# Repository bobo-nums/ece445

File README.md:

# Solar-Powered Traffic Light

Team Members:
- Colin Tarkowski (colinet2)
- Bowen Xiao (bowenx2)
- Richard Przybek (przybek2)

# Problem

Traffic lights are integral to our society, despite their relative lack of innovation over the years. The most significant change has been the switch from incandescent bulbs to LEDs in an attempt to reduce the power consumption of this necessary device. However, this has also led to an increase of light pollution due to the cooler, more intense light emitted by LEDs. They can cause extreme glare and pose a danger to drivers at night. Additionally, the issue of bicyclists and vehicles sharing the road can create many awkward or dangerous situations due to the lack of separation.

# Solution

We propose a solar-powered traffic light system that will solve the issues of drivers and bicyclists sharing the intersection and of light pollution, in addition to reducing consumption of traditional power in two ways. A pressure sensor located near the intersection, such as located upon a nearby curb, will detect whether there is a bicyclist present. Maybe a button instead? The system will be solar powered to minimize utility power utilized during the day. Connection to the grid will be necessary for operation at night or when solar conditions are suboptimal. At night, when light pollution is a significant issue, PWM circuitry will correspondingly dim the LED modules by limiting current. This not only reduces light pollution, but also lowers utility consumption at night.

# Solution Components

## Subsystem 1 - Power

The system will be powered with a solar panel and will include a buck/boost converter to regulate the voltage to 24V. The exact voltage of the panel will depend on what is available in the lab, ideally 24V. Solar power will be generated by ECEB solar panels (if possible) or a purchased module. For backup, we will utilize an AC/DC converter to step the 120VAC utility voltage down to 24VDC. We will also need DC/DC converters to 5V and 3.3V to power the microcontroller and sensors.

## Subsystem 2 - Control
This subsystem will include a microcontroller. It will take data from the pressure sensor (or other used for bicyclists), infrared sensor, and photodiode, process it, and change the traffic lights accordingly.

## Subsystem 3 - Traffic light system
This subsystem will require the aforementioned light modules, all of which can be acquired from a company called Leotek. Their website mentions samples and we hope to be able to utilize the following modules from them: 1x red, 1x yellow, and 3x green 10-28V LED traffic signal modules (see here).

- Additional 2 green modules will be for the bicycle and the walk sign
- If we are unable to acquire these modules, we can construct arrays of the desired LEDs that will operate at the same intended voltage of 24VDC. In this case, the bicycle and walk signs will be constructed with cutouts placed over the module that display the desired shape
- A pressure sensor will be utilized to detect when a bicyclist is at the intersection and an infrared sensor will detect whether a car is at the intersection and how many are present. Alternatively, we could use a camera system to run object detection algorithms on cars and bikes (we could accomplish this using an openMV chip, look into openVx applications, or as a last resort run openCV on a raspberry pi)

# Criterion For Success

A successful project will fulfill the following requirements:

- A standard traffic light (red, yellow, green), a walk light, and a bicycle light controlled on a timer with sensors that adjust the sequence and timing
- An infrared sensor will be utilized to detect when a vehicle is in a given area and the light will then turn green. Pedestrians will be able to press a button to trigger a walk sign shortly afterward
- In order to limit light pollution at night, PWM circuitry will be installed to ensure that the LED is dimmed when the ambient light is sufficiently dark. This will reduce light pollution while reducing the power consumed by the traffic light at night
- Connection to 120VAC grid power will be required to operate the system at night or during cloudy days. System should be able to switch smoothly between solar and grid power
- Will detect traffic flow and adjust timing of lights accordingly, in real time. Vehicle numbers will be detected by the infrared sensor and the timing of the traffic light will be altered autonomously to limit traffic congestion
- Be able to withstand typical weather conditions (waterproof, cold and heat resistant)
- OPTIONAL: Provide manual override to blinking red light for emergency situations
- OPTIONAL: Incorporate MPPT and develop software that will rotate the solar panel along a single access to maximize solar power consumption during the day. This will minimize the need for grid power around dawn and dusk

# NOTE
A system will only be developed for one of the four directions of the intersection, as the other three would simply require equivalent or complementary function. This will also reduce cost and help the project to stay within budget.

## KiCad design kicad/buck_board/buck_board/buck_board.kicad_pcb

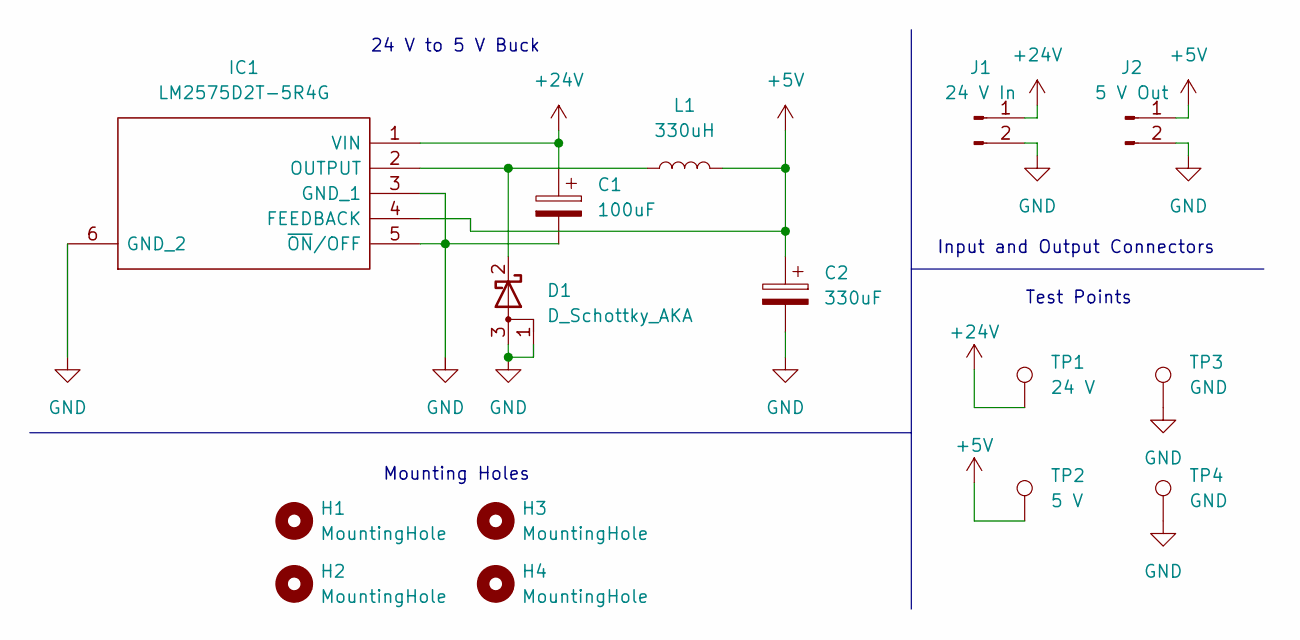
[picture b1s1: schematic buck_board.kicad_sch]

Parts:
C1: 100uF; CP_Radial_D8.0mm_P3.50mm
C2: 330uF; CP_Radial_D8.0mm_P3.50mm
D1: D_Schottky_AKA; TO-252-2
H1, H2, H3, H4: MountingHole; MountingHole_3.2mm_M3
IC1: LM2575D2T-5R4G; NCP5663DSADJR4G; Mouser Part Number 863-LM2575D2T-5R4G
J1: 24 V In; PinHeader_1x02_P2.54mm_Vertical
J2: 5 V Out; PinHeader_1x02_P2.54mm_Vertical
L1: 330uH; L_Toroid_Vertical_L31.8mm_W15.9mm_P13.50mm_Bourns_5700
TP1: 24 V; TestPoint_THTPad_D2.0mm_Drill1.0mm
TP2: 5 V; TestPoint_THTPad_D2.0mm_Drill1.0mm
TP3, TP4: GND; TestPoint_THTPad_D2.0mm_Drill1.0mm

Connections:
+5V: C2.1, IC1.4 (FEEDBACK), J2.1, L1.2, TP2.1
+24V: C1.1, IC1.1 (VIN), J1.1, TP1.1
GND: C1.2, C2.2, D1.1 (A), D1.3 (A), IC1.3 (GND_1), IC1.5 (~ON/OFF), IC1.6 (GND_2), J1.2, J2.2, TP3.1, TP4.1
unnamed: D1.2 (K), IC1.2 (OUTPUT), L1.1

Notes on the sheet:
Input and Output Connectors
Test Points
Mounting Holes
24 V to 5 V Buck

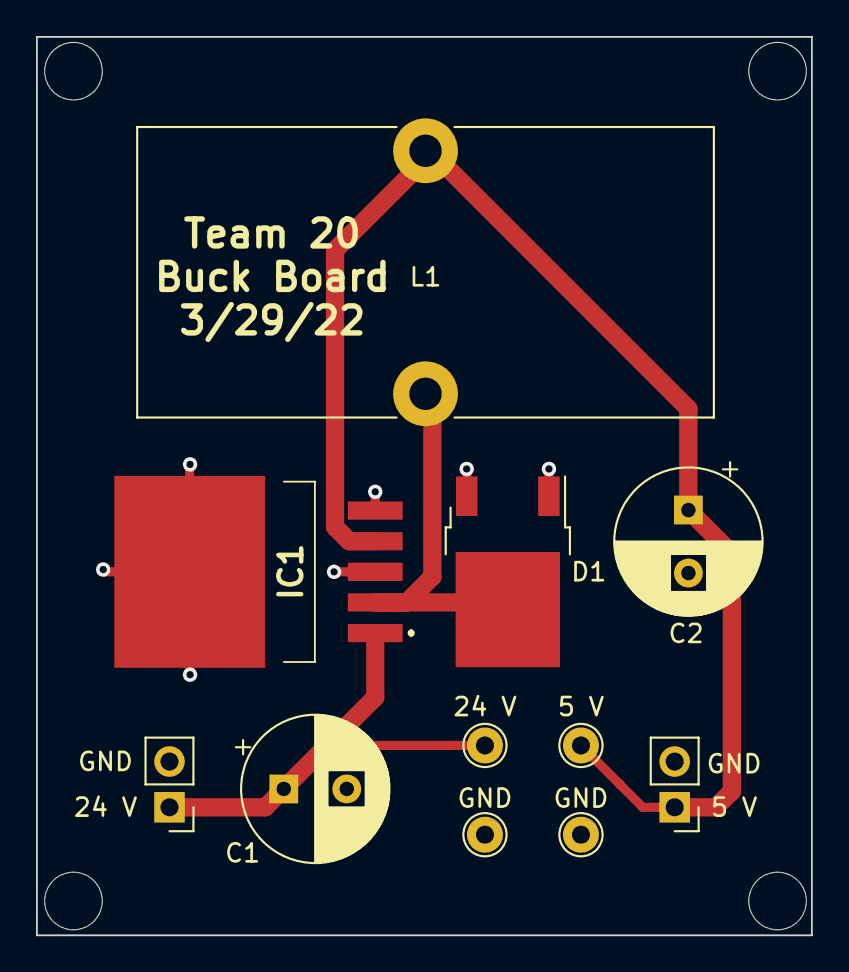
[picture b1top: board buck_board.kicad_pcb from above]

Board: 2 copper layers, 43.1 x 49.9 mm, 15 parts (0 on the bottom side), 4 nets.

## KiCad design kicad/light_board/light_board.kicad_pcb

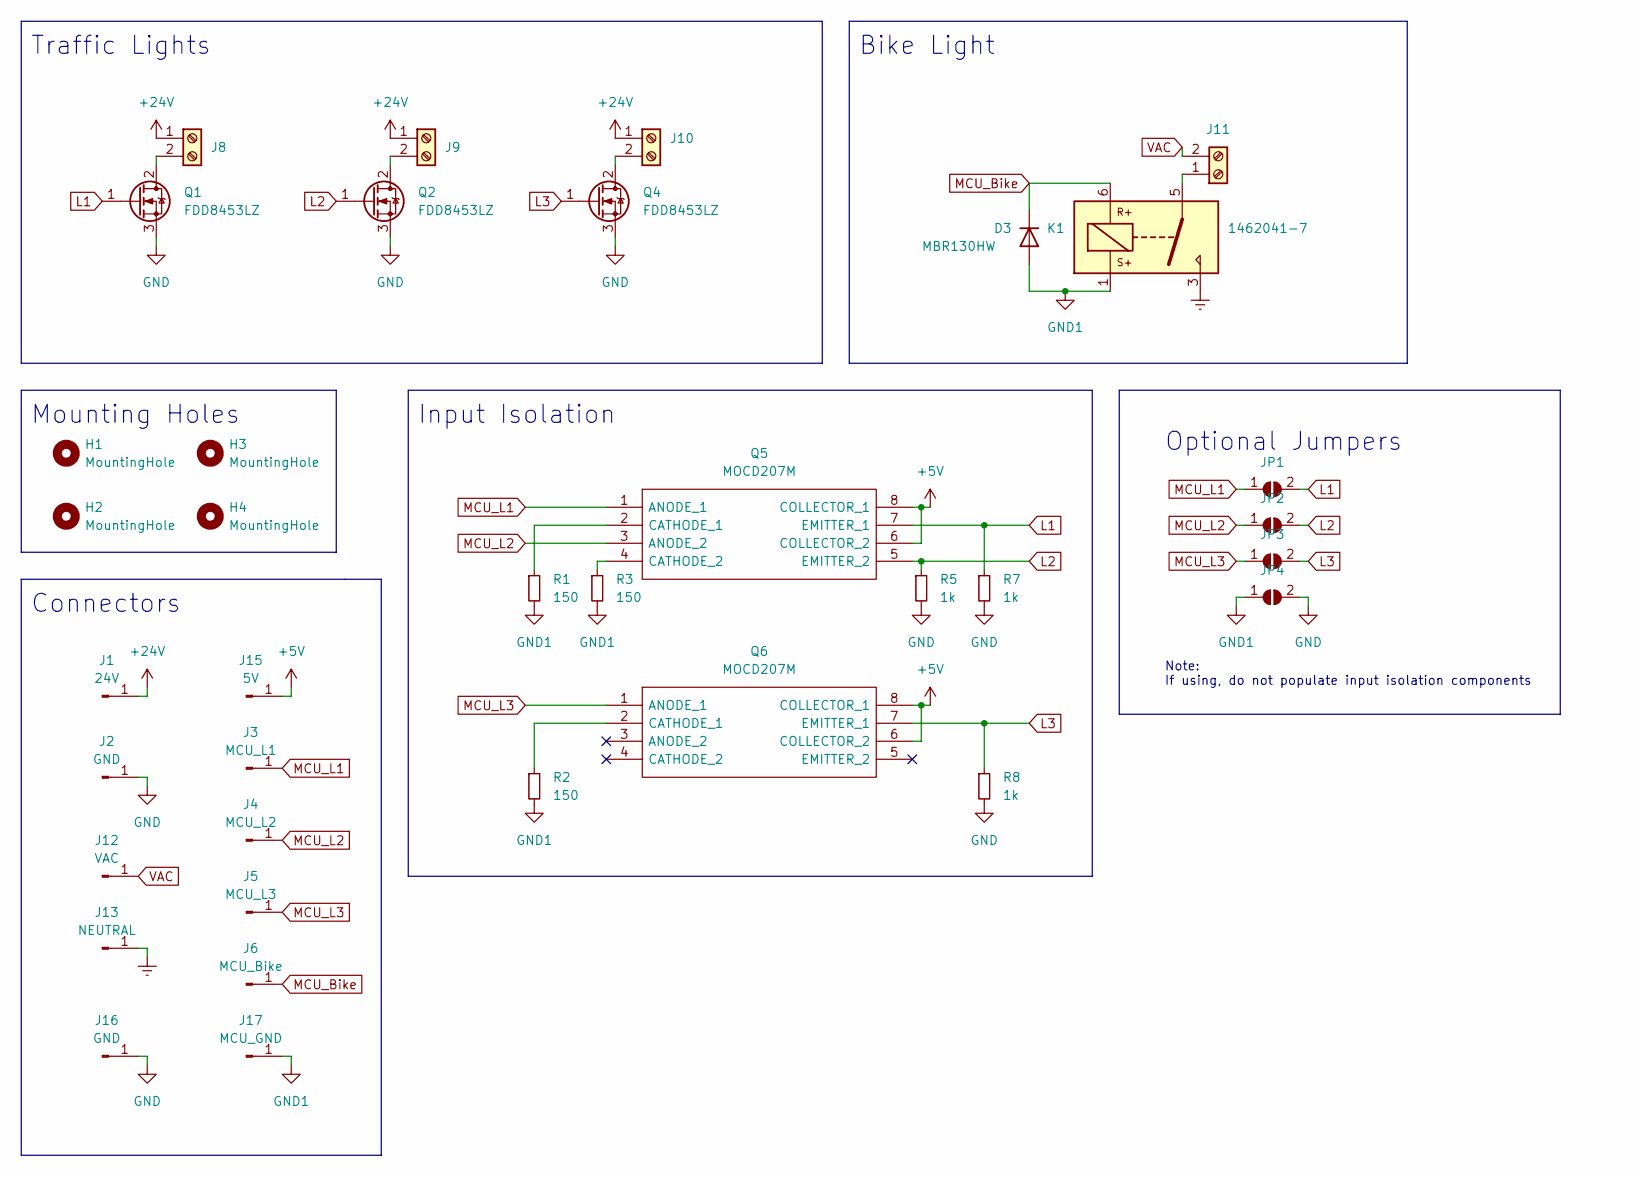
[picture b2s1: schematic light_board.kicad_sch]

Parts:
D3: MBR130HW; D_SOD-123
H1, H2, H3, H4: MountingHole; MountingHole_3.5mm
J1: 24V; hole
J2: GND; hole
J3: MCU_L1; PinHeader_1x01_P2.54mm_Vertical
J4: MCU_L2; PinHeader_1x01_P2.54mm_Vertical
J5: MCU_L3; PinHeader_1x01_P2.54mm_Vertical
J6: MCU_Bike; PinHeader_1x01_P2.54mm_Vertical
J8, J9, J10, J11: Screw_Terminal_01x02; TerminalBlock_Altech_AK300-2_P5.00mm
J12: VAC; hole
J13: NEUTRAL; hole
J15: 5V; PinHeader_1x01_P2.54mm_Vertical
J16: GND; PinHeader_1x01_P2.54mm_Vertical
J17: MCU_GND; PinHeader_1x01_P2.54mm_Vertical
JP1, JP2, JP3, JP4: SolderJumper_2_Open; SolderJumper-2_P1.3mm_Open_TrianglePad1.0x1.5mm
K1: 1462041-7
Q1, Q2, Q4: FDD8453LZ; TO-252-2
Q5, Q6: MOCD207M; SOIC-8_3.9x4.9mm_P1.27mm; Mouser Part Number 512-MOCD207M
R1, R2, R3: 150; R_0603_1608Metric
R5, R7, R8: 1k; R_0603_1608Metric

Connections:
+5V: J15.1, Q5.6 (COLLECTOR_2), Q5.8 (COLLECTOR_1), Q6.6 (COLLECTOR_2), Q6.8 (COLLECTOR_1)
+24V: J1.1, J8.1, J9.1, J10.1
Earth: J13.1, K1.3
GND: J2.1, J16.1, JP4.2 (B), Q1.3 (S), Q2.3 (S), Q4.3 (S), R5.2, R7.2, R8.2
GND1: D3.2 (A), J17.1, JP4.1 (A), K1.1, R1.2, R2.2, R3.2
L1: JP1.2 (B), Q1.1 (G), Q5.7 (EMITTER_1), R7.1
L2: JP2.2 (B), Q2.1 (G), Q5.5 (EMITTER_2), R5.1
L3: JP3.2 (B), Q4.1 (G), Q6.7 (EMITTER_1), R8.1
MCU_Bike: D3.1 (K), J6.1, K1.6
MCU_L1: J3.1, JP1.1 (A), Q5.1 (ANODE_1)
MCU_L2: J4.1, JP2.1 (A), Q5.3 (ANODE_2)
MCU_L3: J5.1, JP3.1 (A), Q6.1 (ANODE_1)
unnamed: J8.2, Q1.2 (D)
unnamed: J9.2, Q2.2 (D)
unnamed: J10.2, Q4.2 (D)
unnamed: J11.1, K1.5
unnamed: Q5.2 (CATHODE_1), R1.1
unnamed: Q5.4 (CATHODE_2), R3.1
unnamed: Q6.2 (CATHODE_1), R2.1
VAC: J11.2, J12.1

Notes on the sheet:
Input Isolation
Mounting Holes
Connectors
Optional Jumpers
Bike Light
Note: If using, do not populate input isolation components
Traffic Lights

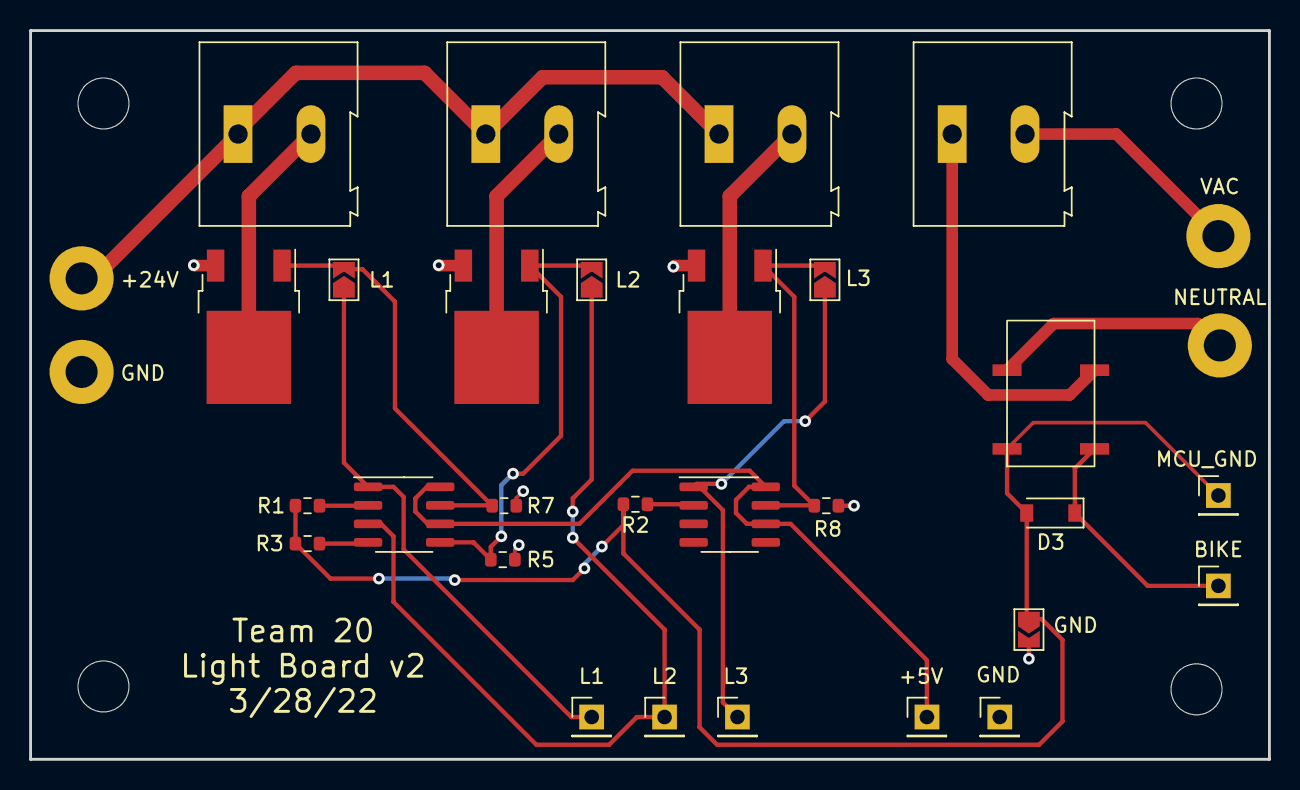
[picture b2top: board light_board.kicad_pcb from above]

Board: 2 copper layers, 85.0 x 50.0 mm, 36 parts (0 on the bottom side), 20 nets.

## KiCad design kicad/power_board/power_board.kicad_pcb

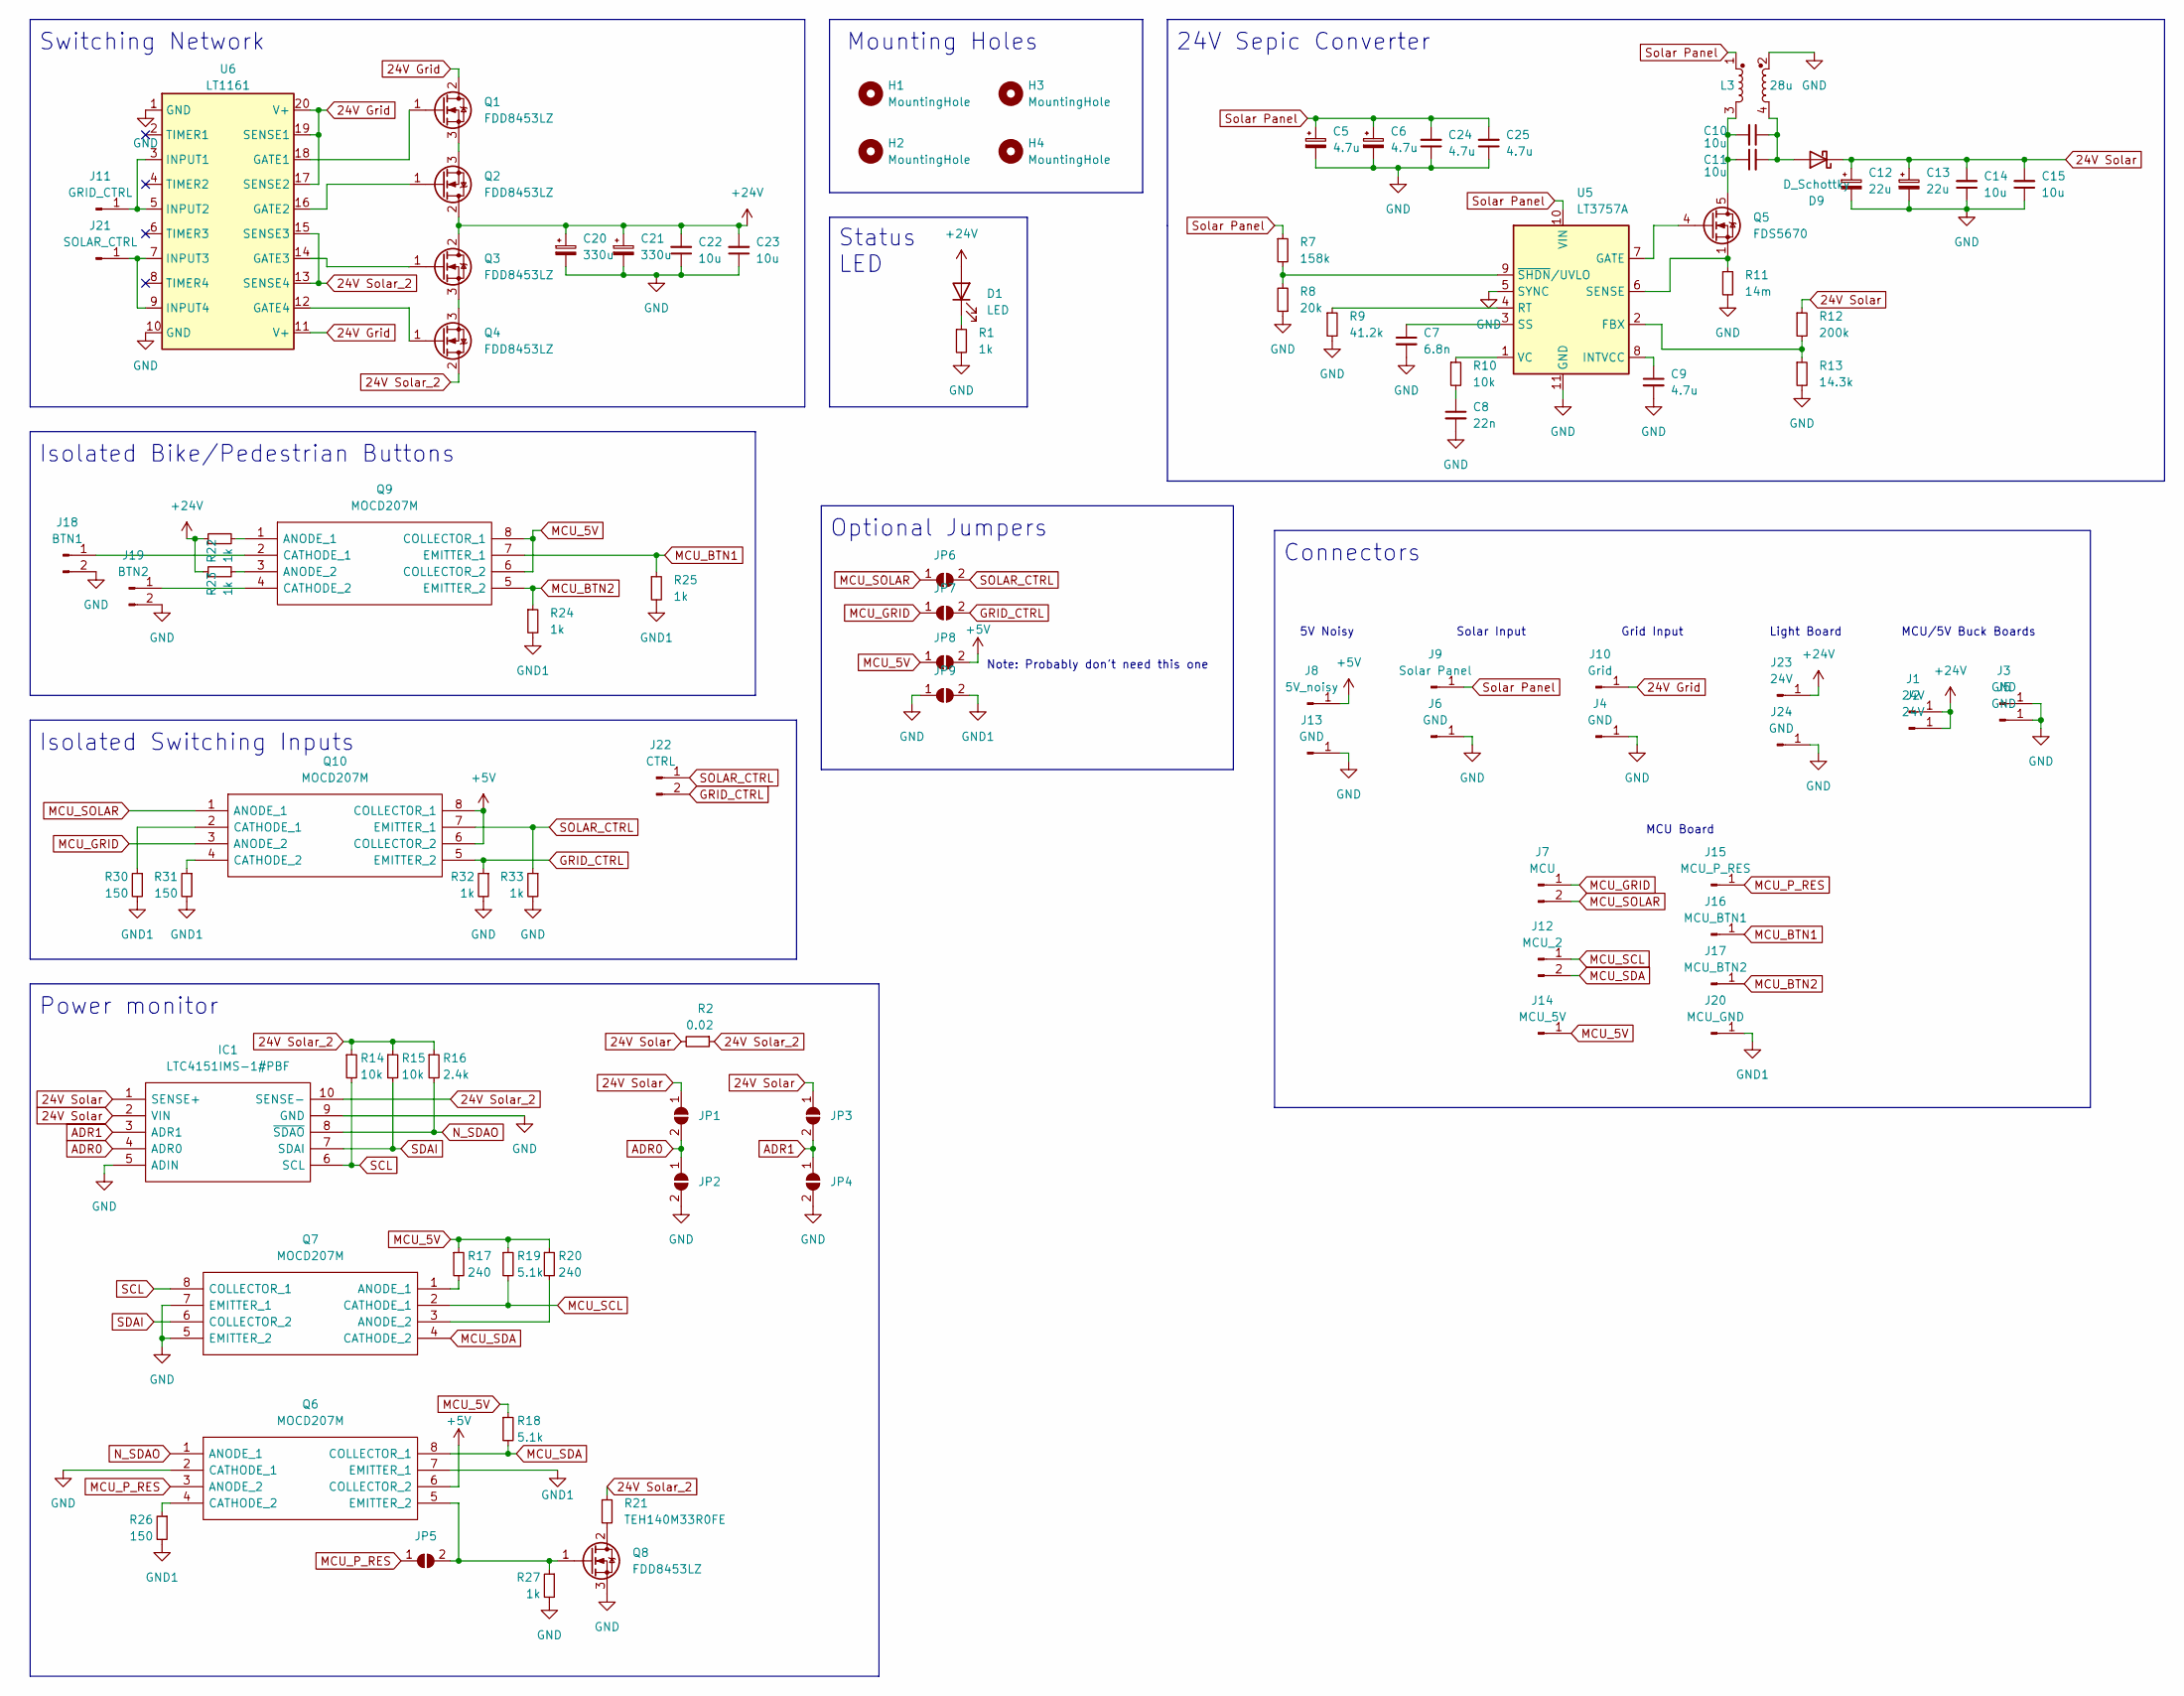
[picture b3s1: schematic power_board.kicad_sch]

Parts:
C5, C6: 4.7u; CP_Radial_D5.0mm_P2.00mm
C7: 6.8n; C_0603_1608Metric
C8: 22n; C_0603_1608Metric
C9, C24, C25: 4.7u; C_0805_2012Metric
C10, C11, C14, C15, C22, C23: 10u; C_1210_3225Metric
C12, C13: 22u; CP_Radial_D5.0mm_P2.50mm
C20, C21: 330u; C_Radial_D16.0mm_H25.0mm_P7.50mm
D1: LED; C_0603_1608Metric
D9: D_Schottky; TO-252-2
H1, H2, H3, H4: MountingHole; MountingHole_3.5mm
IC1: LTC4151IMS-1#PBF; MSOP-10_3x3mm_P0.5mm; Mouser Part Number 584-LTC4151IMS-1#PBF
J1, J2: 24V; PinHeader_1x01_P2.54mm_Vertical
J3, J5, J13: GND; PinHeader_1x01_P2.54mm_Vertical
J4, J24: GND; hole
J6: GND; hole_1.6mm
J7: MCU; PinHeader_1x02_P2.54mm_Vertical
J8: 5V_noisy; PinHeader_1x01_P2.54mm_Vertical
J9: Solar Panel; hole_1.6mm
J10: Grid; hole
J11: GRID_CTRL; PinHeader_1x01_P2.54mm_Vertical
J12: MCU_2; PinHeader_1x02_P2.54mm_Vertical
J14: MCU_5V; PinHeader_1x01_P2.54mm_Vertical
J15: MCU_P_RES; PinHeader_1x01_P2.54mm_Vertical
J16: MCU_BTN1; PinHeader_1x01_P2.54mm_Vertical
J17: MCU_BTN2; PinHeader_1x01_P2.54mm_Vertical
J18: BTN1; PinHeader_1x02_P2.54mm_Vertical
J19: BTN2; PinHeader_1x02_P2.54mm_Vertical
J20: MCU_GND; PinHeader_1x01_P2.54mm_Vertical
J21: SOLAR_CTRL; PinHeader_1x01_P2.54mm_Vertical
J22: CTRL; PinHeader_1x02_P2.54mm_Vertical
J23: 24V; hole
JP1, JP2, JP3, JP4, JP5, JP6, JP7, JP8, JP9: SolderJumper_2_Open; SolderJumper-2_P1.3mm_Open_TrianglePad1.0x1.5mm
L3: 28u; PF0553NL
Q1, Q2, Q3, Q4, Q8: FDD8453LZ; TO-252-2
Q5: FDS5670; SOIC-8_3.9x4.9mm_P1.27mm
Q6, Q7, Q9, Q10: MOCD207M; SOIC-8_3.9x4.9mm_P1.27mm; Mouser Part Number 512-MOCD207M
R1, R22, R23, R24, R25, R27, R32, R33: 1k; R_0603_1608Metric
R2: 0.02; R_0603_1608Metric
R7: 158k; R_0603_1608Metric
R8: 20k; R_0603_1608Metric
R9: 41.2k; R_0603_1608Metric
R10, R14, R15: 10k; R_0603_1608Metric
R11: 14m; R_2512_6332Metric
R12: 200k; R_1206_3216Metric
R13: 14.3k; R_0603_1608Metric
R16: 2.4k; R_0603_1608Metric
R17, R20: 240; R_0603_1608Metric
R18, R19: 5.1k; R_0603_1608Metric
R21: TEH140M33R0FE; TEH140
R26, R30, R31: 150; R_0603_1608Metric
U5: LT3757A; MSOP-10-1EP_3x3mm_P0.5mm_EP1.68x1.88mm
U6: LT1161; SOIC-20W_7.5x12.8mm_P1.27mm

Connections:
24V Grid: J10.1, Q1.2 (D), U6.11 (V+), U6.17 (SENSE2), U6.19 (SENSE1), U6.20 (V+)
24V Solar: C12.1, C13.1, C14.2, C15.2, D9.2 (K), IC1.1 (SENSE+), IC1.2 (VIN), JP1.1 (A), JP3.1 (A), R2.2, R12.1
24V Solar_2: IC1.10 (SENSE-), Q4.2 (D), R2.1, R14.1, R15.1, R16.1, R21.1, U6.13 (SENSE4), U6.15 (SENSE3)
+5V: J8.1, JP8.2 (B), Q6.6 (COLLECTOR_2), Q10.6 (COLLECTOR_2), Q10.8 (COLLECTOR_1)
+24V: C20.1, C21.1, C22.2, C23.2, D1.2 (A), J1.1, J2.1, J23.1, Q2.2 (D), Q3.2 (D), R22.1, R23.1
ADR0: IC1.4 (ADR0), JP1.2 (B), JP2.1 (A)
ADR1: IC1.3 (ADR1), JP3.2 (B), JP4.1 (A)
GND: C5.2, C6.2, C7.2, C8.2, C9.2, C12.2, C13.2, C14.1, C15.1, C20.2, C21.2, C22.1, C23.1, C24.1, C25.1, IC1.5 (ADIN), IC1.9 (GND), J3.1, J4.1, J5.1, J6.1, J13.1, J18.2, J19.2, J24.1, JP2.2 (B), JP4.2 (B), JP9.1 (A), L3.2, Q6.2 (CATHODE_1), Q7.5 (EMITTER_2), Q7.7 (EMITTER_1), Q8.3 (S), R1.2, R8.1, R9.2, R11.2, R13.2, R27.2, R32.2, R33.2, U5.5 (SYNC), U5.11 (GND), U6.1 (GND), U6.10 (GND)
GND1: J20.1, JP9.2 (B), Q6.7 (EMITTER_1), R24.2, R25.2, R26.2, R30.2, R31.2
GRID_CTRL: J22.2, JP7.2 (B), Q10.5 (EMITTER_2), R32.1
MCU_5V: J14.1, JP8.1 (A), Q9.6 (COLLECTOR_2), Q9.8 (COLLECTOR_1), R17.1, R18.1, R19.1, R20.1
MCU_BTN1: J16.1, Q9.7 (EMITTER_1), R25.1
MCU_BTN2: J17.1, Q9.5 (EMITTER_2), R24.1
MCU_GRID: J7.1, JP7.1 (A), Q10.3 (ANODE_2)
MCU_P_RES: J15.1, JP5.1 (A), Q6.3 (ANODE_2)
MCU_SCL: J12.1, Q7.2 (CATHODE_1), R19.2
MCU_SDA: J12.2, Q6.8 (COLLECTOR_1), Q7.4 (CATHODE_2), R18.2
MCU_SOLAR: J7.2, JP6.1 (A), Q10.1 (ANODE_1)
N_SDAO: IC1.8 (~SDAO), Q6.1 (ANODE_1), R16.2
unnamed: C7.1, U5.3 (SS)
unnamed: C8.1, R10.2
unnamed: C9.1, U5.8 (INTVCC)
unnamed: C10.1, C11.2, D9.1 (A), L3.4
unnamed: C10.2, C11.1, L3.3, Q5.5 (D), Q5.6 (S), Q5.7 (S), Q5.8 (S)
unnamed: D1.1 (K), R1.1
unnamed: J11.1, U6.3 (INPUT1), U6.5 (INPUT2)
unnamed: J18.1, Q9.2 (CATHODE_1)
unnamed: J19.1, Q9.4 (CATHODE_2)
unnamed: J21.1, U6.7 (INPUT3), U6.9 (INPUT4)
unnamed: Q1.1 (G), U6.18 (GATE1)
unnamed: Q1.3 (S), Q2.3 (S)
unnamed: Q2.1 (G), U6.16 (GATE2)
unnamed: Q3.1 (G), U6.14 (GATE3)
unnamed: Q3.3 (S), Q4.3 (S)
unnamed: Q4.1 (G), U6.12 (GATE4)
unnamed: Q5.1 (S), Q5.2 (S), Q5.3 (S), R11.1, U5.6 (SENSE)
unnamed: Q5.4 (G), U5.7 (GATE)
unnamed: Q6.4 (CATHODE_2), R26.1
unnamed: JP5.2 (B), Q6.5 (EMITTER_2), Q8.1 (G), R27.1
unnamed: Q7.1 (ANODE_1), R17.2
unnamed: Q7.3 (ANODE_2), R20.2
unnamed: Q8.2 (D), R21.2
unnamed: Q9.1 (ANODE_1), R22.2
unnamed: Q9.3 (ANODE_2), R23.2
unnamed: Q10.2 (CATHODE_1), R30.1
unnamed: Q10.4 (CATHODE_2), R31.1
unnamed: R7.2, R8.2, U5.9 (~SHDN/UVLO)
unnamed: R9.1, U5.4 (RT)
unnamed: R10.1, U5.1 (VC)
unnamed: R12.2, R13.1, U5.2 (FBX)
SCL: IC1.6 (SCL), Q7.8 (COLLECTOR_1), R14.2
SDAI: IC1.7 (SDAI), Q7.6 (COLLECTOR_2), R15.2
SOLAR_CTRL: J22.1, JP6.2 (B), Q10.7 (EMITTER_1), R33.1
Solar Panel: C5.1, C6.1, C24.2, C25.2, J9.1, L3.1, R7.1, U5.10 (VIN)

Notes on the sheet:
MCU Board
Power monitor
24V Sepic Converter
Note: Probably don't need this one
Connectors
Status LED
Isolated Switching Inputs
Solar Input
Mounting Holes
Grid Input
5V Noisy
Light Board
Isolated Bike/Pedestrian Buttons
Optional Jumpers
MCU/5V Buck Boards
Switching Network

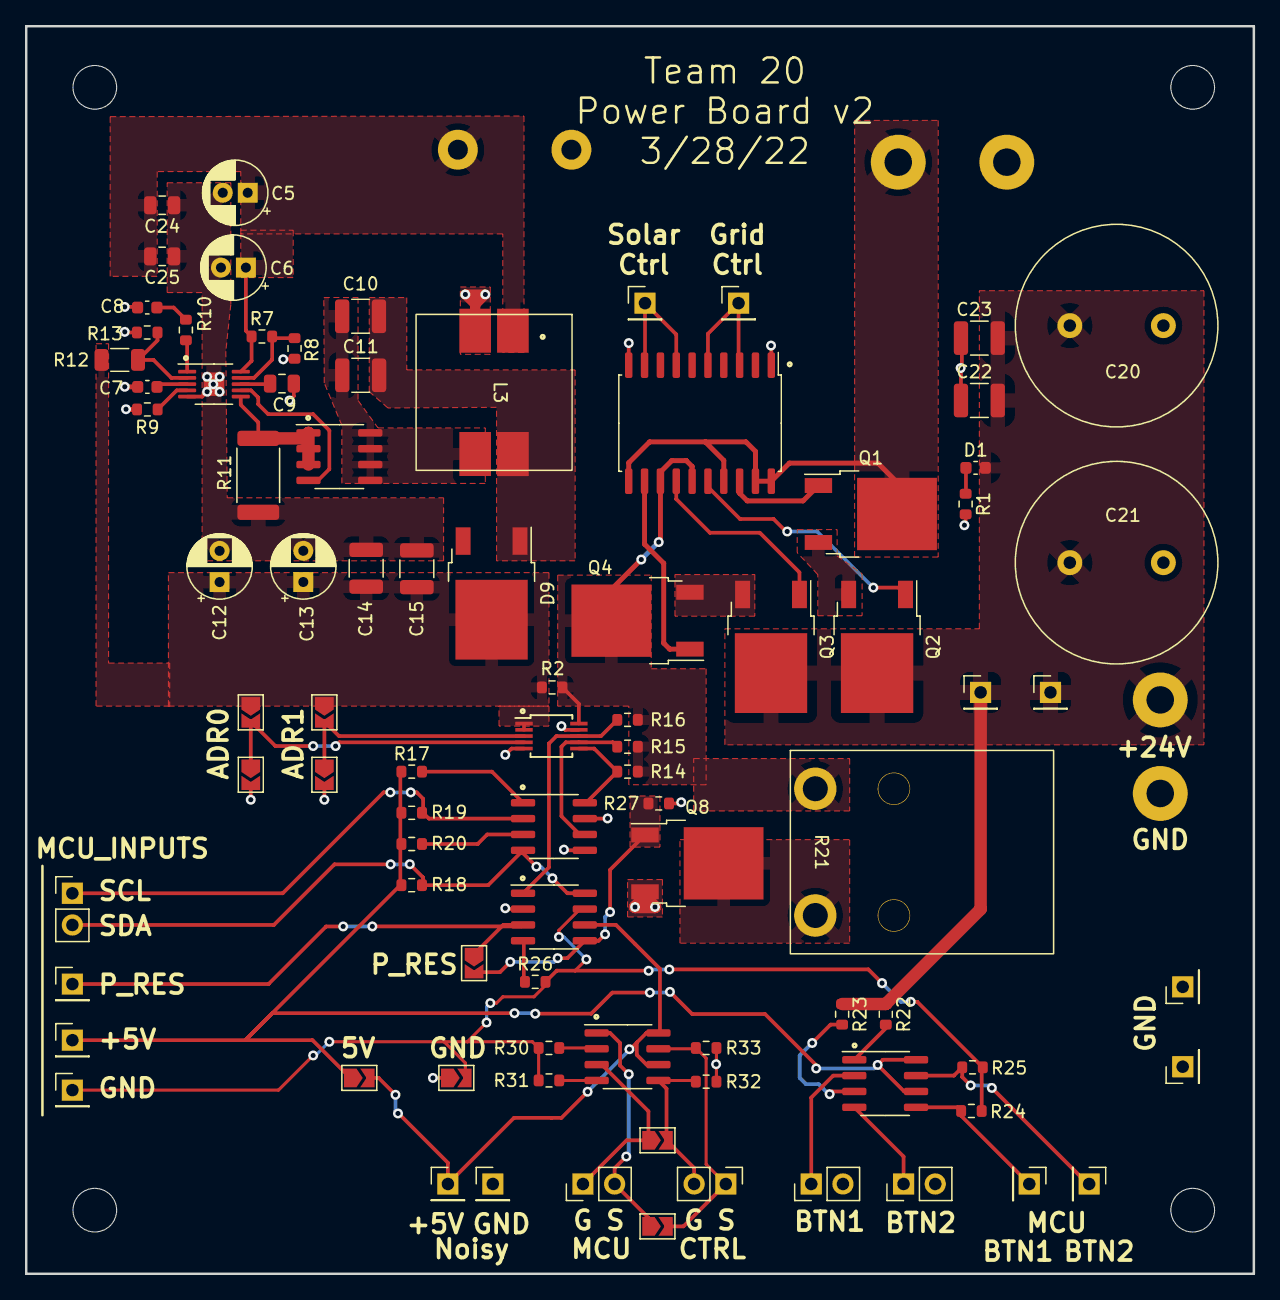
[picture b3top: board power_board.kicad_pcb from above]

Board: 2 copper layers, 98.4 x 100.0 mm, 97 parts (0 on the bottom side), 54 nets.

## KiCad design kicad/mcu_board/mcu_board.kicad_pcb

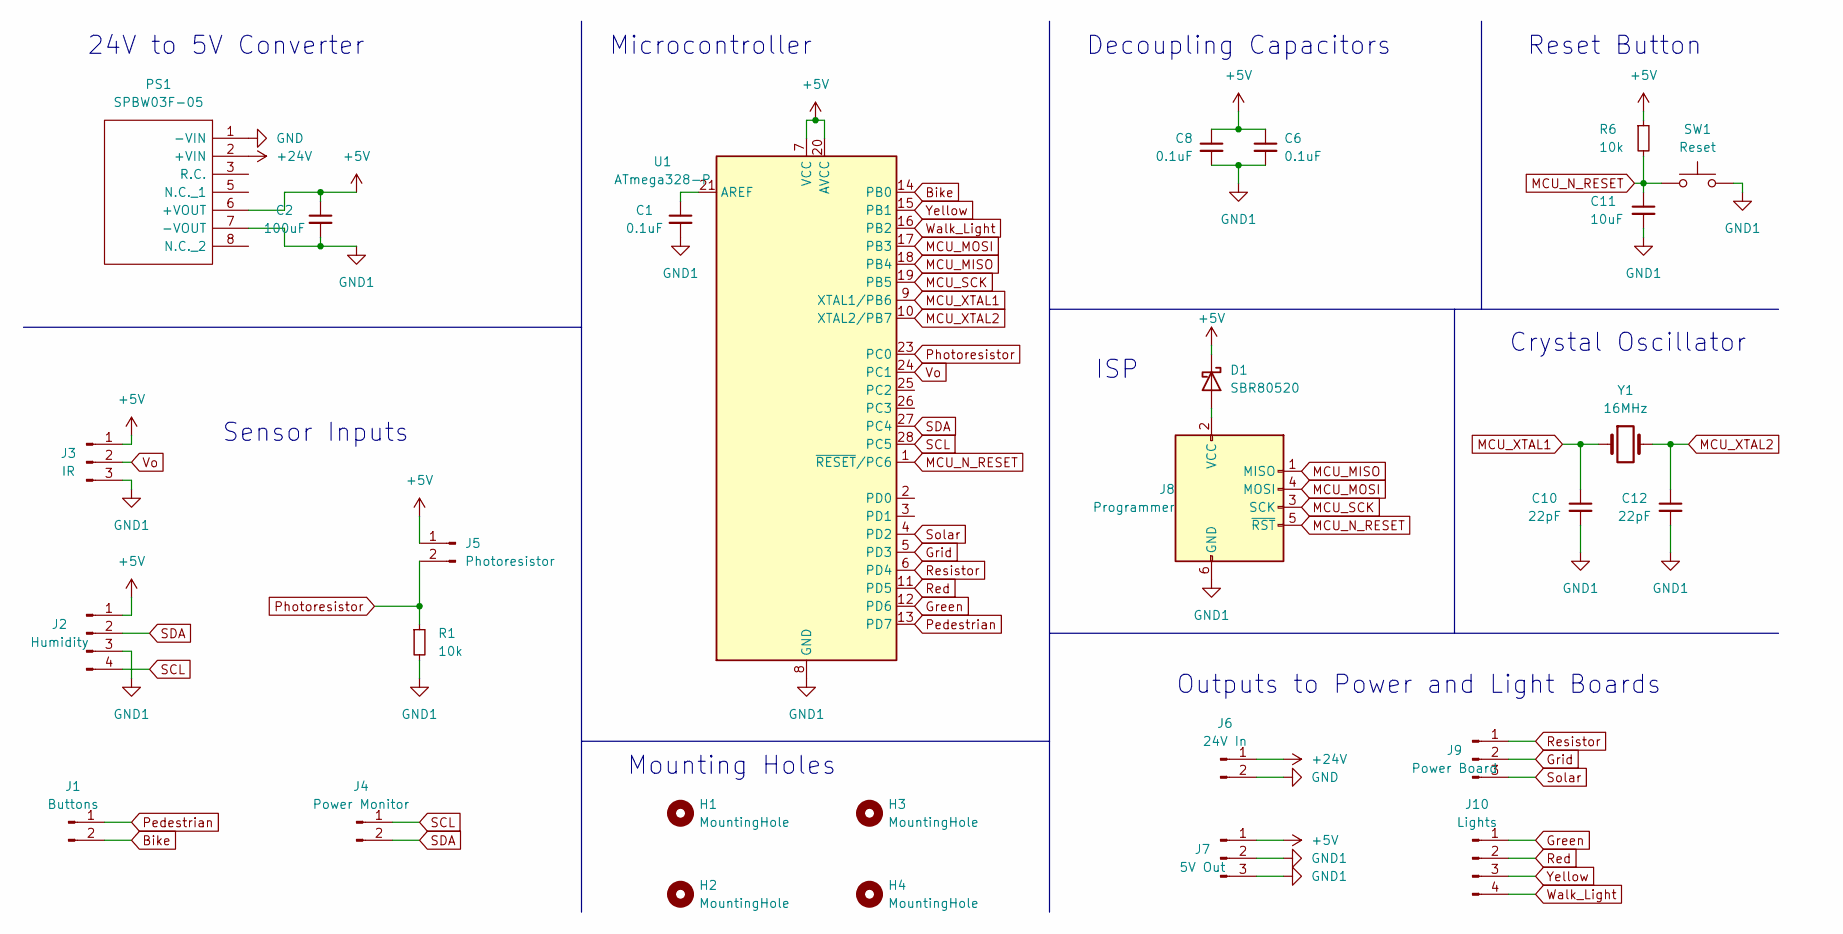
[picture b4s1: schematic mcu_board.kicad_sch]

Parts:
C1, C6, C8: 0.1uF; C_0603_1608Metric_Pad1.08x0.95mm_HandSolder
C2: 100uF; C_1206_3216Metric_Pad1.33x1.80mm_HandSolder
C10, C12: 22pF; C_0603_1608Metric_Pad1.08x0.95mm_HandSolder
C11: 10uF; C_0603_1608Metric_Pad1.08x0.95mm_HandSolder
D1: SBR80520; D_SOD-123
H1, H2, H3, H4: MountingHole; MountingHole_3.2mm_M3
J1: Buttons; PinHeader_1x02_P2.54mm_Vertical
J2: Humidity; PinHeader_1x04_P2.54mm_Vertical
J3: IR; PinHeader_1x03_P2.54mm_Vertical
J4: Power Monitor; PinHeader_1x02_P2.54mm_Vertical
J5: Photoresistor; PinHeader_1x02_P2.54mm_Vertical
J6: 24V In; PinHeader_1x02_P2.54mm_Vertical
J7: 5V Out; PinHeader_1x03_P2.54mm_Vertical
J8: Programmer; IDC-Header_2x03_P2.54mm_Vertical
J9: Power Board; PinHeader_1x03_P2.54mm_Vertical
J10: Lights; PinHeader_1x04_P2.54mm_Vertical
PS1: SPBW03F-05; SPBW06F05; Mouser Part Number 709-SPBW03F-05
R1, R6: 10k; R_0805_2012Metric_Pad1.20x1.40mm_HandSolder
SW1: Reset; SW_SPST_TL3305B
U1: ATmega328-P; DIP-28_W7.62mm
Y1: 16MHz; Crystal_HC49-U_Vertical

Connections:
+5V: C2.1, C6.1, C8.1, D1.1 (K), J2.1, J3.1, J5.1, J7.1, PS1.6 (+VOUT), R6.1, U1.7 (VCC), U1.20 (AVCC)
+24V: J6.1, PS1.2 (+VIN)
Bike: J1.2, U1.14 (PB0)
GND: J6.2, PS1.1 (-VIN)
GND1: C1.2, C2.2, C6.2, C8.2, C10.2, C11.2, C12.2, J2.3, J3.3, J7.2, J7.3, J8.6 (GND), PS1.7 (-VOUT), R1.2, SW1.2, U1.8 (GND), U1.22 (GND)
Green: J10.1, U1.12 (PD6)
Grid: J9.2, U1.5 (PD3)
MCU_MISO: J8.1 (MISO), U1.18 (PB4)
MCU_MOSI: J8.4 (MOSI), U1.17 (PB3)
MCU_N_RESET: C11.1, J8.5 (~RST), R6.2, SW1.1, U1.1 (~RESET/PC6)
MCU_SCK: J8.3 (SCK), U1.19 (PB5)
MCU_XTAL1: C10.1, U1.9 (XTAL1/PB6), Y1.1
MCU_XTAL2: C12.1, U1.10 (XTAL2/PB7), Y1.2
unnamed: C1.1, U1.21 (AREF)
unnamed: D1.2 (A), J8.2 (VCC)
Pedestrian: J1.1, U1.13 (PD7)
Photoresistor: J5.2, R1.1, U1.23 (PC0)
Red: J10.2, U1.11 (PD5)
Resistor: J9.1, U1.6 (PD4)
SCL: J2.4, J4.1, U1.28 (PC5)
SDA: J2.2, J4.2, U1.27 (PC4)
Solar: J9.3, U1.4 (PD2)
Vo: J3.2, U1.24 (PC1)
Walk_Light: J10.4, U1.16 (PB2)
Yellow: J10.3, U1.15 (PB1)

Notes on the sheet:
ISP
Outputs to Power and Light Boards
Mounting Holes
Crystal Oscillator
Reset Button
24V to 5V Converter
Decoupling Capacitors
Sensor Inputs
Microcontroller

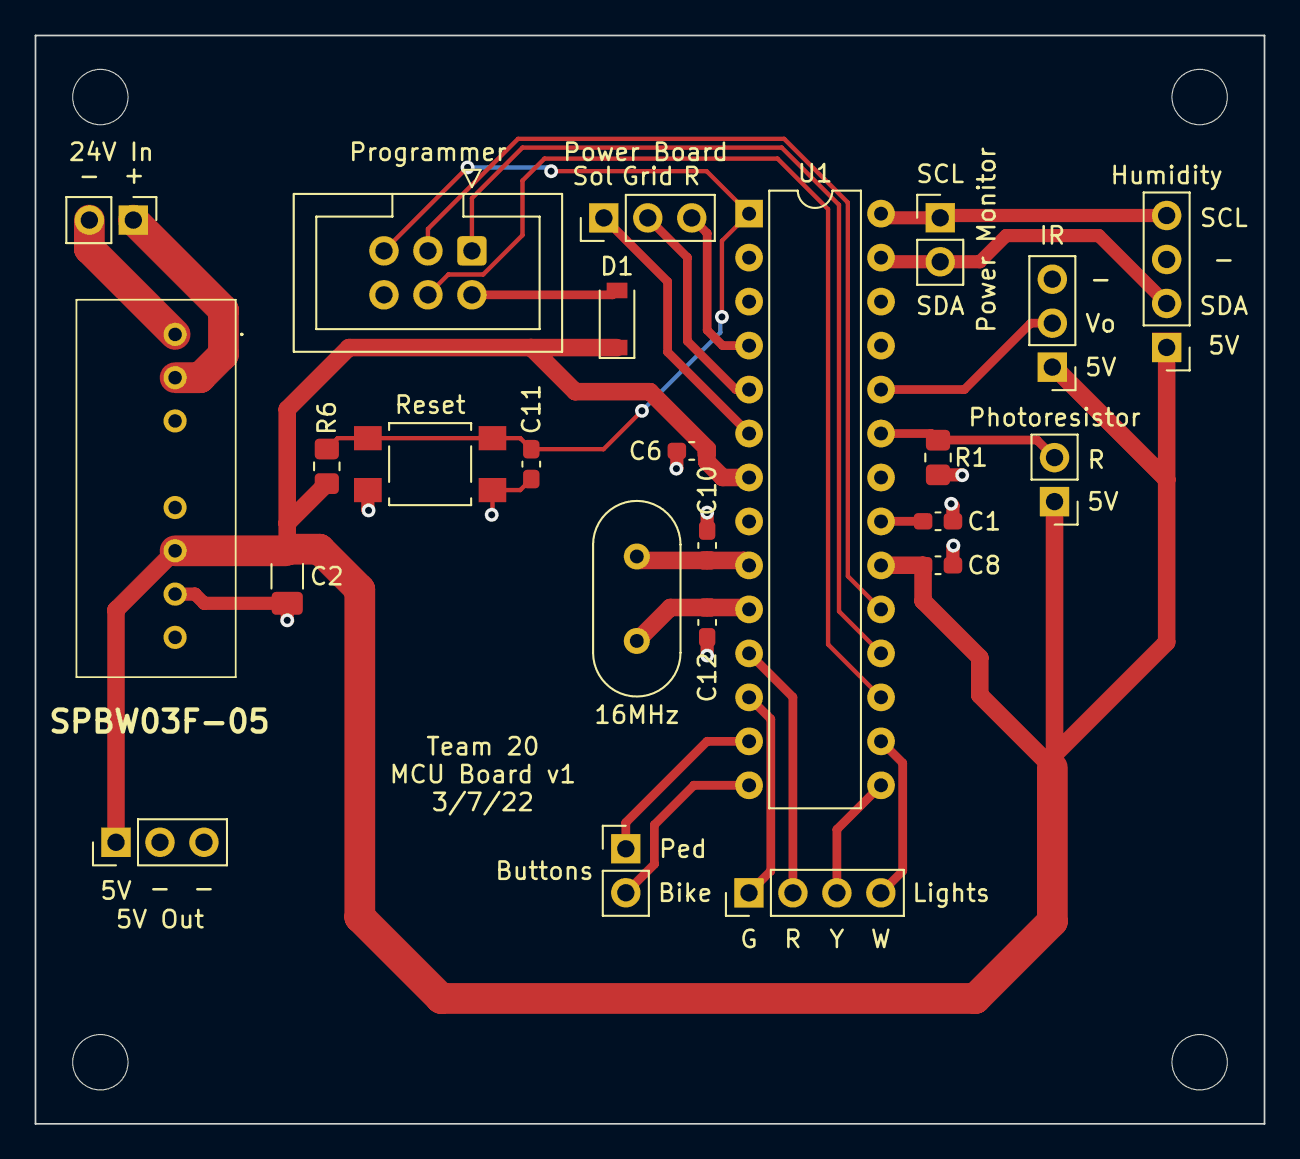
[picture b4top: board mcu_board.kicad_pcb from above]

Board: 2 copper layers, 71.0 x 62.9 mm, 28 parts (0 on the bottom side), 25 nets.

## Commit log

2022-01-24 add directories
2022-01-24 add initial logs
2022-02-06 initial RFA
2022-02-06 fig1removed
2022-02-08 added first notebook entry, need to add images
2022-02-08 added visual aid.png
2022-02-08 Added block_diagramV1
2022-02-08 add image links to markdown
2022-02-08 added newline char after paragraph
2022-02-08 added newline, attempt #2
2022-02-08 2/7/22
2022-02-08 updated 2/7/22 with LDR vs photodiode
2022-02-09 add 2/8/22
2022-02-10 2/9/22
2022-02-10 added first ta meeting
2022-02-10 fixed heading format issue
2022-02-10 add datasheet dir
2022-02-10 adding power switching datasheet
2022-02-10 another datasheet
2022-02-15 add datasheets + kicad
2022-02-15 temp 2/14/22
2022-02-15 added microcontroller schematic
2022-02-15 2/14/22
2022-02-15 add button + power boards
2022-02-16 removed backups, added buck converters
2022-02-16 adding datasheets
2022-02-16 adding to spreadsheet
2022-02-16 adding more datasheets
2022-02-17 updating readme
2022-02-17 added ltc4359 ckt + components
2022-02-17 minor changes
2022-02-18 adding components
2022-02-20 add simulations
2022-02-22 Added photoresistor datasheet
2022-02-22 Renamed photoresistor pdf
2022-02-22 removed old photoresistor pdf
2022-02-22 new switching network
2022-02-22 Added second TA meeting and writing up design doc
2022-02-23 2/22/22
2022-02-23 fixing switching network
2022-02-23 added physical design
2022-02-24 Added sensing components and mcu
2022-02-24 Added phototransistor
2022-02-24 sepic and switching network
2022-02-24 another switching network
2022-02-24 Added tables made for design doc
2022-02-24 added tables from cost analysis section
2022-02-24 uploaded first version of control flow diagram
2022-02-24 added control flow table and reformatted figures
2022-02-24 Reformatted figures
2022-02-25 screenshots and adding components
2022-02-28 adding images
2022-02-28 more images
2022-03-01 power board pcb
2022-03-01 2/28/22
2022-03-02 light board
2022-03-02 traffic lights WIP
2022-03-03 MCU board WIP
2022-03-03 light board done
2022-03-03 adding symbols
2022-03-06 added isolation to power and light boards
2022-03-07 working on MCU
2022-03-08 finished up MCU board
2022-03-08 add light/power gerbers
2022-03-08 finishing up MCU and adding gerbers
2022-03-09 Working on notebook
2022-03-22 Added rough draft of control code
2022-03-22 Added library to read from humidity sensor
2022-03-24 3/23/22
2022-03-26 light board v2 wip, 3/25/22
2022-03-27 Added state machine and bike interrupt
2022-03-28 3/26/22
2022-03-28 light board v2
2022-03-29 update pcbs
2022-03-29 3/28/22
2022-03-29 add light/power pcb gerbers
2022-03-30 buck board done
2022-03-30 updating lab notebook through 3/29
2022-03-31 3/29 and 3/30
2022-04-04 add ipr and some photos
2022-04-08 fixed button interrupt, ir sensor working
2022-04-15 4/15
2022-04-18 Added notes from last month
2022-04-18 added dimensions sketch
2022-04-18 added dimensions sketch to markdown
2022-04-18 added png dimensions sketch
2022-04-18 added code blocks
2022-04-18 4/18
2022-04-19 added some pictures
2022-04-19 added photos to markdown
2022-04-21 4/19, 4/20
2022-04-21 Clean up, all sensors active
2022-04-24 Tuned sensors, added bike flicker
2022-04-24 bowne notebook
2022-04-24 Added last couple days
2022-04-25 data + 4/24
2022-04-25 Finishing touches, fixed edge cases
2022-04-25 Added arduinoISP serial pass through code
2022-04-29 data
2022-05-05 done with lab notebook
2022-05-05 actually done with notebook
